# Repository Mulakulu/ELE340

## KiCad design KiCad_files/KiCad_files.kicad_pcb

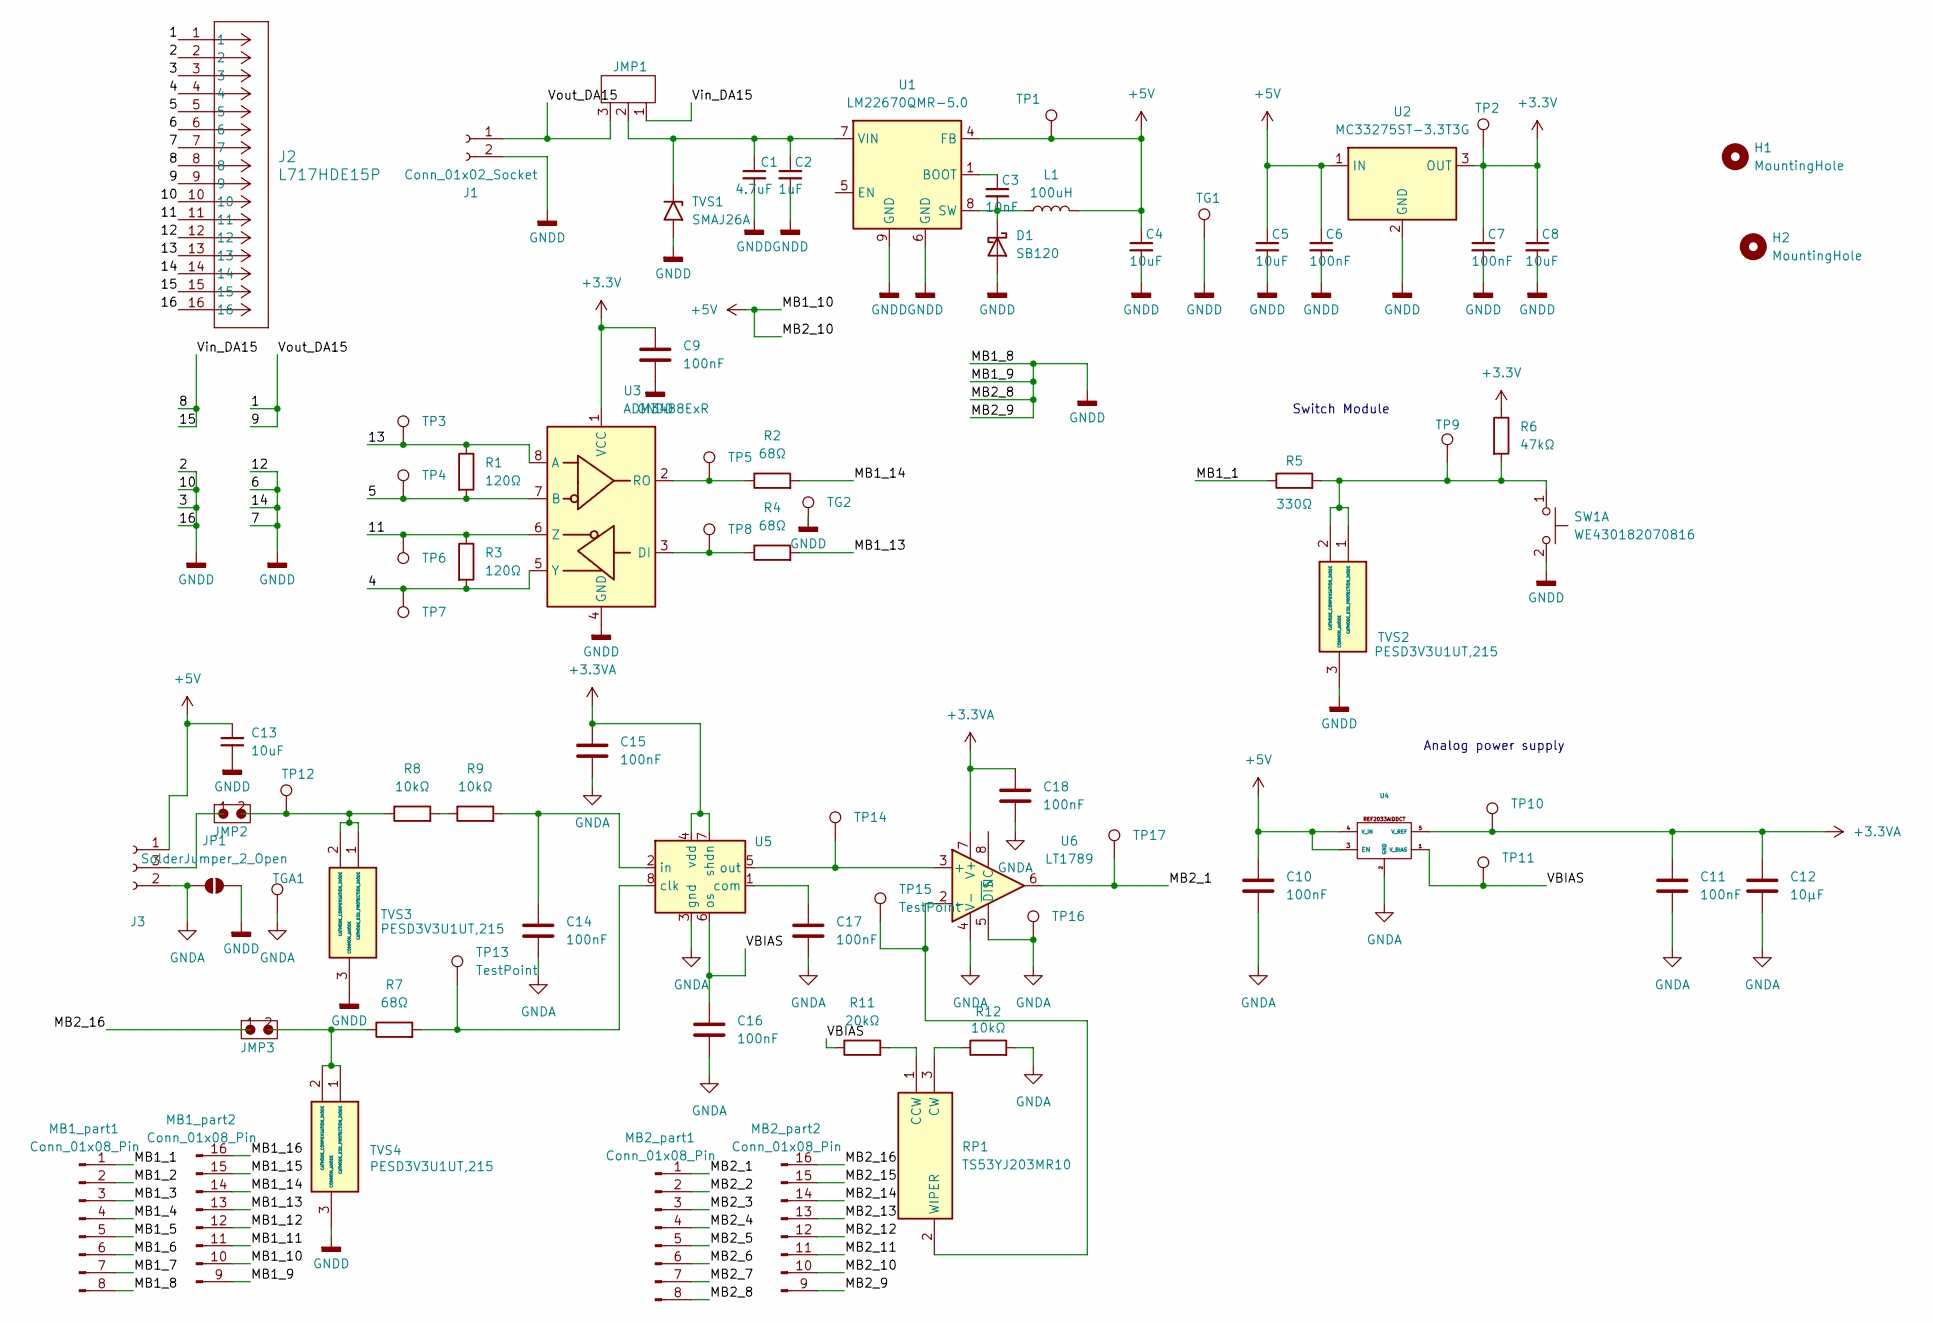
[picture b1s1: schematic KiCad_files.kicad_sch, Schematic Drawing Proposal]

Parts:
C1: 4.7uF; C_1206_3216Metric_Pad1.33x1.80mm_HandSolder
C2: 1uF; C_1206_3216Metric_Pad1.33x1.80mm_HandSolder
C3: 10nF; C_1206_3216Metric_Pad1.33x1.80mm_HandSolder
C4, C5, C8, C13: 10uF; C_1210_3225Metric_Pad1.33x2.70mm_HandSolder
C6, C7, C9, C10, C11, C14, C15, C16, C17, C18: 100nF; C_1206_3216Metric_Pad1.33x1.80mm_HandSolder
C12: 10μF; C_1210_3225Metric_Pad1.33x2.70mm_HandSolder
D1: SB120; D_MicroSMP_AK
H1, H2: MountingHole; MountingHole_3.2mm_M3
J1: Conn_01x02_Socket; SL35290G
J2: L717HDE15P; 15PinDsub
J3: Conn_01x03_Socket; Pin_Header_1x3_P3.5mm
JMP1: Pin_Header_1x3_P2.54mm
JMP2, JMP3: Pin_Header_2x1_P2.54mm_Vertical
JP1: SolderJumper_2_Open; SolderJumper-2_P1.3mm_Open_RoundedPad1.0x1.5mm
L1: 100uH; SDR2207
MB1_part1, MB2_part1: Conn_01x08_Pin; MB1x8Pins
MB1_part2, MB2_part2: Conn_01x08_Pin; MB1x8Pins_part2
R1, R3: 120Ω; R_1206_3216Metric_Pad1.30x1.75mm_HandSolder
R2, R4, R7: 68Ω; R_1206_3216Metric_Pad1.30x1.75mm_HandSolder
R5: 330Ω; R_1206_3216Metric_Pad1.30x1.75mm_HandSolder
R6: 47kΩ; R_1206_3216Metric_Pad1.30x1.75mm_HandSolder
R8, R9, R12: 10kΩ; R_1206_3216Metric_Pad1.30x1.75mm_HandSolder
R11: 20kΩ; R_1206_3216Metric_Pad1.30x1.75mm_HandSolder
RP1: TS53YJ203MR10; TS53YJ; Manufacturer_Part_Number TS53YJ203MR10
SW1: WE430182070816; Switch WE430182070816
TG1, TG2: TestPoint; testpoint_1.4mm
TGA1: TestPoint; testpoint_1.4mm
TP1, TP2, TP3, TP4, TP5, TP6, TP7, TP8, TP12, TP13, TP14, TP15, TP16, TP17: TestPoint; testpoint_1.4mm
TP9, TP10, TP11: testpoint_1.4mm
TVS1: SMAJ26A; D_SMA
TVS2, TVS3, TVS4: PESD3V3U1UT,215; SOT95P230X110-3N; Manufacturer_Part_Number PESD3V3U1UT,215
U1: LM22670QMR-5.0; SOIC-8-1EP_3.9x4.9mm_P1.27mm_EP2.41x3.81mm
U2: MC33275ST-3.3T3G; SOT-223-3_TabPin2
U3: ADM3488ExR; SOIC-8_3.9x4.9mm_P1.27mm
U4: SOT-23-5
U5: SOIC-8_3.9x4.9mm_P1.27mm
U6: LT1789; SOIC-8_3.9x4.9mm_P1.27mm

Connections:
+3.3V: C7.1, C8.1, C9.1, R6.1, TP2.1, U2.3 (OUT), U3.1 (VCC)
+3.3VA: C11.1, C12.1, C15.1, C18.1, TP10.1, U4.5 (V_REF), U5.4 (vdd), U5.7 (shdn), U6.7 (V+)
+5V: C4.1, C5.1, C6.1, C10.1, C13.1, J3.1, L1.2, MB1_part2.10 (Pin_7), MB2_part2.10 (Pin_7), TP1.1, U1.4 (FB), U2.1 (IN), U4.3 (EN), U4.4 (V_IN)
/1: J1.1, J2.1, J2.9, JMP1.3
/4: J2.4, R3.2, TP7.1, U3.5 (Y)
/5: J2.5, R1.2, TP4.1, U3.7 (B)
/11: J2.11, R3.1, TP6.1, U3.6 (Z)
/13: J2.13, R1.1, TP3.1, U3.8 (A)
/15: J2.8, J2.15, JMP1.1
/MB1_1: MB1_part1.1, R5.1
/MB1_2: MB1_part1.2
/MB1_3: MB1_part1.3
/MB1_4: MB1_part1.4
/MB1_5: MB1_part1.5
/MB1_6: MB1_part1.6
/MB1_7: MB1_part1.7
/MB1_11: MB1_part2.11 (Pin_6)
/MB1_12: MB1_part2.12 (Pin_5)
/MB1_13: MB1_part2.13 (Pin_4), R4.2
/MB1_14: MB1_part2.14 (Pin_3), R2.2
/MB1_15: MB1_part2.15 (Pin_2)
/MB1_16: MB1_part2.16 (Pin_1)
/MB2_1: MB2_part1.1, TP17.1, U6.6
/MB2_2: MB2_part1.2
/MB2_3: MB2_part1.3
/MB2_4: MB2_part1.4
/MB2_5: MB2_part1.5
/MB2_6: MB2_part1.6
/MB2_7: MB2_part1.7
/MB2_11: MB2_part2.11 (Pin_6)
/MB2_12: MB2_part2.12 (Pin_5)
/MB2_13: MB2_part2.13 (Pin_4)
/MB2_14: MB2_part2.14 (Pin_3)
/MB2_15: MB2_part2.15 (Pin_2)
/MB2_16: JMP3.1, MB2_part2.16 (Pin_1)
/VBIAS: C16.1, R11.1, TP11.1, U4.1 (V_BIAS), U5.6 (os)
GNDA: C10.2, C11.2, C12.2, C14.2, C15.2, C16.2, C17.2, C18.2, J3.2 (Pin_3), JP1.1 (A), R12.2, TGA1.1, TP16.1, U4.2 (GND), U5.3 (gnd), U6.4 (V-), U6.5 (~DIS)
GNDD: C1.2, C2.2, C4.2, C5.2, C6.2, C7.2, C8.2, C9.2, C13.2, D1.2 (A), J1.2, J2.2, J2.3, J2.6, J2.7, J2.10, J2.12, J2.14, J2.16, JP1.2 (B), MB1_part1.8, MB1_part2.9 (Pin_8), MB2_part1.8, MB2_part2.9 (Pin_8), SW1.2 (D), TG1.1, TG2.1, TVS1.2 (A2), TVS2.3 (COMMON_ANODE), TVS3.3 (COMMON_ANODE), TVS4.3 (COMMON_ANODE), U1.6 (GND), U1.9 (GND), U2.2 (GND), U3.4 (GND)
unnamed: C3.2, D1.1 (K), L1.1, U1.8 (SW)
unnamed: J3.3 (Pin_2), JMP2.1
unnamed: R8.2, R9.1
unnamed: R11.2, RP1.1 (CCW)
unnamed: R12.1, RP1.3 (CW)
unnamed: RP1.2 (WIPER), TP15.1, U6.2 (-)
unnamed: R5.2, R6.2, SW1.1 (C), TP9.1, TVS2.1 (CATHODE_ESD_PROTECTION_DIODE), TVS2.2 (CATHODE_COMPENSATION_DIODE)
unnamed: C1.1, C2.1, JMP1.2, TVS1.1 (A1), U1.7 (VIN)
unnamed: JMP2.2, R8.1, TP12.1, TVS3.1 (CATHODE_ESD_PROTECTION_DIODE), TVS3.2 (CATHODE_COMPENSATION_DIODE)
unnamed: JMP3.2, R7.1, TVS4.1 (CATHODE_ESD_PROTECTION_DIODE), TVS4.2 (CATHODE_COMPENSATION_DIODE)
unnamed: C3.1, U1.1 (BOOT)
unnamed: R4.1, TP8.1, U3.3 (DI)
unnamed: R2.1, TP5.1, U3.2 (RO)
unnamed: R7.2, TP13.1, U5.8 (clk)
unnamed: C17.1, U5.1 (com)
unnamed: C14.1, R9.2, U5.2 (in)
unnamed: TP14.1, U5.5 (out), U6.3 (+)

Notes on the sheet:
Switch Module
Analog power supply

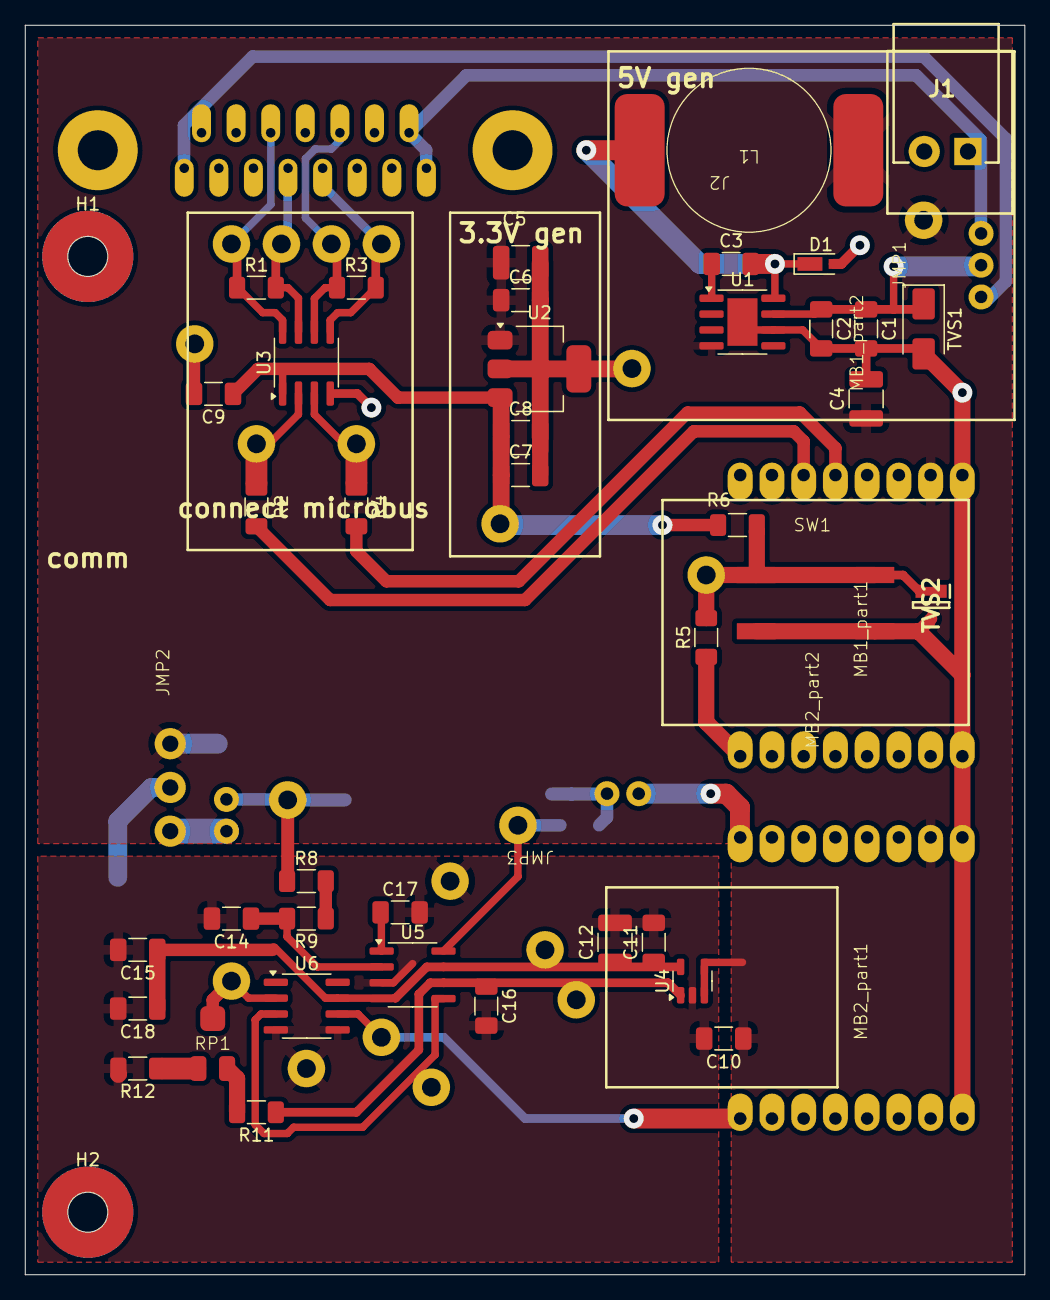
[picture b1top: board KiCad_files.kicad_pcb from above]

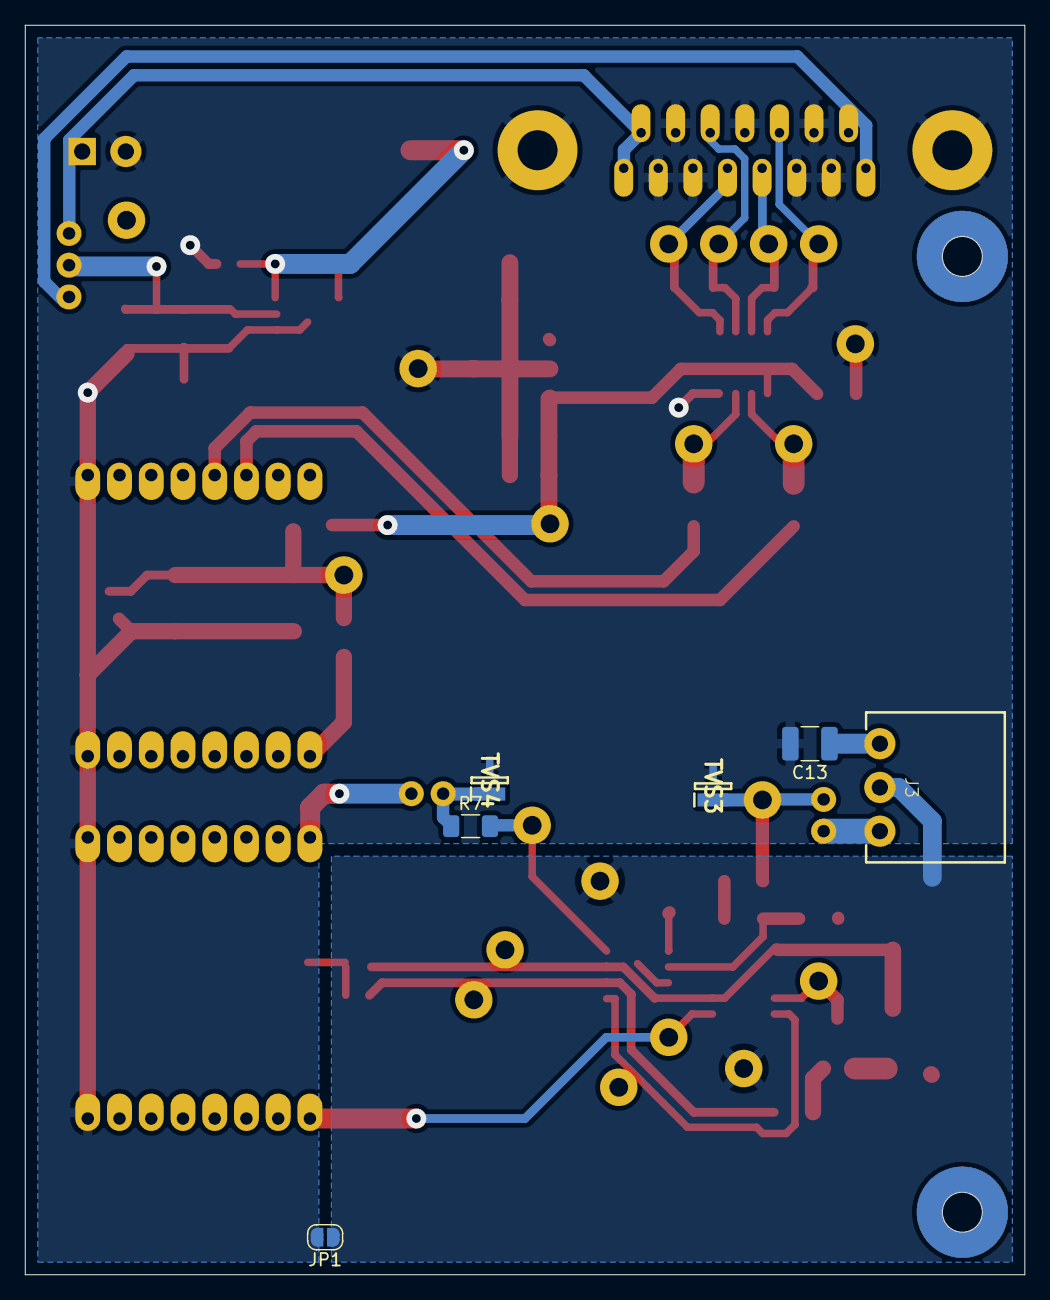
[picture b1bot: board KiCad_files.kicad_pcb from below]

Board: 2 copper layers, 80.0 x 100.0 mm, 76 parts (6 on the bottom side), 34 nets.

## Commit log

2024-09-05 i did this and this
2024-09-07 Added P3 to reposetory
2024-09-24 Added kicad folder and files
2024-09-24 Re-added kicad files
2024-09-24 removed trash copy
2024-09-24 added schematic file
2024-09-24 blablabla
2024-09-24 test
2024-09-24 added the analog power supply to the main scheme
2024-09-24 Added digital power supply to schematic
2024-09-24 minimal changes
2024-09-24 i changed the ground to gnda on the analog power supply
2024-09-24 i inserted the RS422 communication circuit to the mains scheme
2024-09-25 The switch Module done!
2024-09-26 Made the schematic somewhat presentable and filled out the last bit of the circuit
2024-09-26 SchematicEdits
2024-09-27 Added stm32 project back in
2024-10-01 Not sure how much I've done in the STM32
2024-10-01 Added kontroll node project
2024-10-01 ACTUALLY added the kontroll node project
2024-10-01 Small changes to avbrotsmetodar
2024-10-03 updating the memes
2024-10-03 i implemented functions for receiving data
2024-10-03 Added a fucntional communication
2024-10-08 added a pcb design file
2024-10-08 i inserted some footprints
2024-10-08 added L footprint
2024-10-08 added pcb file
2024-10-08 changed the switch and what's under it
2024-10-08 meme
2024-10-08 Added project library
2024-10-08 Added library.pretty to the library list
2024-10-08 Actually added the footprint tables for sharing
2024-10-08 added footprint for pin headers and updated footprints
2024-10-08 fixed all resistor footprints
2024-10-08 added testpoint footprint
2024-10-08 i made a footprint for jmp1
2024-10-08 MB1x8 footprin
2024-10-08 Added footprints to testpoints
2024-10-08 updated library
2024-10-15 i fixed all of the errors from the schematic design
2024-10-15 fixed references and labels
2024-10-17 worked on the pcb design details
2024-10-17 fixed pcb design details
2024-10-17 added pcb design file
2024-10-17 Alligned microbus on PCB
2024-10-17 Created 15pinDsubMeme
2024-10-17 Added schematic model to 15pindsub
2024-10-17 added footprints
2024-10-17 Minor work on the PCB
2024-10-21 fixed J3
2024-10-21 Updated some of the PCB
2024-10-21 Significant progress on the PCB
2024-10-21 some footprints(maybe)
2024-10-22 placed some testpoints and shortened nets
2024-10-22 Some more progress on the PCB
2024-10-22 placed components and drew lines
2024-10-22 Completed first version of the PCB
2024-10-23 Minor changes to the PCB and added a problems list
2024-10-23 Forgot to save. Lol
2024-10-23 Unremarkable changes
2024-10-24 Minor changes to problems with the PCB
2024-10-24 documented errors
2024-10-25 changed the errors file
2024-10-28 Added line to problems
2024-10-29 fixed one footprint
2024-10-29 added an error note
2024-10-31 checked for errors in the analog circuit
2024-11-05 Fixed all 'problems'
2024-11-06 Finalizing the PCB. Fixed mounting holes and flipped some components to the other side so jumpers can be soldered easily
2024-11-29 Added a stm32 project with a working ADC
2024-12-01 Added clock signal and smoothing function for the ADC in the sensor node
2024-12-06 A functional state of the system with a simple P controller
2024-12-06 Added kontroll node for the final product
2024-12-06 Double check
2024-12-06 Idk man
2024-12-06 New attempt on sharing project files in the Archive Files folder
